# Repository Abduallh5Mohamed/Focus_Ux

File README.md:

# FOCUS — ابدأ من هنا

## تجربة النسخة الحالية على Windows

لتشغيل الواجهة والـAPI محليًا مع الـGPU والأصول الموجودة، من غير تعديل التثبيت القديم:
**[خطوات التجربة المحلية](docs/LOCAL_WINDOWS_TRIAL.md)**.
الوضع شبه المباشر تجريبي ومقفول افتراضيًا؛ اختبارات الكود مش إثباتًا للأداء الحقيقي.

خطة تنفيذ للمطورين الأربعة، 29 أكتوبر 2026. **منتج Upload/PWA كامل في اليوم الأول، تحسين ومحاولة معالجة أثناء التسجيل في اليوم الثاني.**

الأقسام التالية خطة التنفيذ الأصلية والمراجع؛ التطبيق الحالي داخل `product/`.
ده مش إعلان جاهزية للنشر أو اجتياز تجربة الـGPU.

## ترتيب القراءة
1. [الخطة الكاملة](docs/00_MASTER_PLAN.md).
2. [ما نستخدمه من القديم وكيف ننقله](docs/01_LEGACY_AND_MIGRATION.md).
3. [العقود المشتركة](docs/02_CONTRACTS.md) — يثبتها الفريق في أول ساعة.
4. كل مطور يقرأ ملفه ويبدأ مستقلًا:
   - [Dev 1 — ML Worker](docs/DEV1_ML.md)
   - [Dev 2 — API والنشر](docs/DEV2_BACKEND.md)
   - [Dev 3 — PWA والإدخال](docs/DEV3_PWA.md)
   - [Dev 4 — النتيجة والدمج](docs/DEV4_RESULTS_INTEGRATION.md)
5. [النشر والتشغيل](docs/03_DEPLOYMENT.md) و[بوابة الوضع المباشر](docs/04_REALTIME_GATE.md).

## الموجود هنا
- `legacy_snapshot/`: نسخ صغيرة من السكريبتات والتقارير والنتائج المرجعية، لا تعدّلها.
- `legacy_manifest.json`: مصدر كل ملف وSHA256 للتحقق.
- `docs/`: المهام والعقود وخطة التسليم.

## الموجود أصلًا ولا نعيد تنزيله
- `A:/focus/.venv`: البيئة التشغيلية؛ افحصها قبل الاعتماد عليها، ولا تنسخها بين الأجهزة.
- `A:/focus/Dolphin`: الكود والأصول.
- `A:/focus/cache`: cache؛ افحص المسارات المستخدمة فعليًا للأوزان، ولا تفترض أن كل الأوزان هنا.
- `A:/focus/data/gt5`: بيانات المقارنة ومراجعها.
- `C:/Users/abdua/WorkBuddy AI/2026-10-27-00-17-28`: تقارير الاختبارات القديمة.

## مكان البناء المقترح
ابنوا داخل `A:/فوكس/product/` بمستودع Git جديد مستقل عن التجارب. لم تُنشأ هذه الخدمة أو فروع Git بواسطة كتابة الخطة. أول شخص يجهّز المستودع هو Dev 4، ويشارك الفريق عبر مستودع خاص إن متاح.

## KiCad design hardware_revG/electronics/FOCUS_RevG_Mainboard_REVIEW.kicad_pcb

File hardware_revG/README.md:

# FOCUS RevG review package

An original everyday-eyewear design direction for the FOCUS assistive-listening concept, with a separate engineering packaging screen. The styling image is visual only. **No hardware was built or measured; this is not a release candidate.**

## Open first

1. [Visual design direction](INDUSTRIAL_DESIGN_DIRECTION.md) and [viewer-right camera style concept](previews/FOCUS_RevG_camera_right_concept.png).
2. [Compact CAD assembly review](mechanical/compact_direction/RevG_assembly_review.svg), [native FreeCAD](mechanical/compact_direction/FOCUS_RevG_Compact_Packaging_Screen.FCStd), [STEP](mechanical/compact_direction/FOCUS_RevG_Compact_Packaging_Screen.step), and [check data](mechanical/compact_direction/cad_checks.json). The native file has saved GUI visibility/colors/isometric view; if regenerating geometry with FreeCADCmd, run `mechanical/compact_direction/make_view_ready.FCMacro` in the GUI again before delivery.
3. [Engineering change plan](REV_G_CHANGE_PLAN.md), [open issues](REV_G_ASSUMPTIONS_AND_OPEN_ISSUES.md), and [release blockers](docs/DFM_AND_RELEASE_BLOCKERS.md).
4. [Electronics status](electronics/ENGINEERING_STATUS.md), [KiCad schematic](electronics/FOCUS_RevG_Mainboard_REVIEW.kicad_sch), [KiCad PCB](electronics/FOCUS_RevG_Mainboard_REVIEW.kicad_pcb), [ERC](electronics/reports/ERC.rpt), [DRC](electronics/reports/DRC.rpt).
5. [Candidate BOM](BOM.csv), [cost model](COST_MODEL.md), and [test plan](TEST_PLAN.md).

## Critical result

The compact CAD lowered the **partial assumed** mass from 98.86 g to 90.51 g, but still breaches the 60 g target and 70 g conditional ceiling before required unweighed parts. Folding and antenna fit fail. The partial KiCad drawing fails ERC/DRC and is bench-sized. Neither CAD nor electronics is ready for fabrication; styling and engineering currently diverge.

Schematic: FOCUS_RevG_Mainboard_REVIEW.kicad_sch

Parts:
C1, C2, C3, C4, C21, C22: 100nF X7R 10V; C_0603_1608Metric; MPN UNSELECTED
C10, C11, C12, C13: 1uF X7R 10V AC coupling; C_0603_1608Metric; MPN UNSELECTED
C20: 10uF X7R 10V; C_0603_1608Metric; MPN UNSELECTED
J1: P4 PDM host OPEN GPIO map; PinHeader_1x05_P2.54mm_Vertical; MPN UNSELECTED
J2: External regulated AMP rail 3.0V; PinHeader_1x02_P2.54mm_Vertical; MPN UNSELECTED
J3: External DAC differential analog; PinHeader_1x05_P2.54mm_Vertical; MPN UNSELECTED
J4: Host control 3V3; watchdog OPEN; PinHeader_1x05_P2.54mm_Vertical; MPN UNSELECTED
J5: HARD MUTE dry-contact switch; PinHeader_1x02_P2.54mm_Vertical; MPN UNSELECTED
J6: EXTERNAL open drain supervisor; PinHeader_1x02_P2.54mm_Vertical; MPN UNSELECTED
J7: Left BTL floating pair; PinHeader_1x02_P2.54mm_Vertical; MPN UNSELECTED
J8: Right BTL floating pair; PinHeader_1x02_P2.54mm_Vertical; MPN UNSELECTED
MK1, MK2, MK3, MK4: IM69D130 4x3x1.2 mm; Infineon_PG-LLGA-5-1; MPN IM69D130V01XTSA1
R1: 33R clock damping candidate; R_0603_1608Metric; MPN UNSELECTED
R10, R12, R14, R16: 100k 1% attenuation; R_0603_1608Metric; MPN UNSELECTED
R11, R13, R15, R17: 1k 1% attenuation; R_0603_1608Metric; MPN UNSELECTED
R20, R21: 4k7 candidate I2C pullup; R_0603_1608Metric; MPN UNSELECTED
R22: 10k host enable isolation; R_0603_1608Metric; MPN UNSELECTED
R23: 47k DEFAULT MUTE pulldown; R_0603_1608Metric; MPN UNSELECTED
TP1: MIC_3V3; TestPoint_Pad_D1.0mm; MPN UNSELECTED
TP2: PDM_CLK; TestPoint_Pad_D1.0mm; MPN UNSELECTED
TP3: PDM_D01; TestPoint_Pad_D1.0mm; MPN UNSELECTED
TP4: PDM_D23; TestPoint_Pad_D1.0mm; MPN UNSELECTED
TP5: AMP_3V0; TestPoint_Pad_D1.0mm; MPN UNSELECTED
TP6: AMP_SDZ; TestPoint_Pad_D1.0mm; MPN UNSELECTED
TP7: GND; TestPoint_Pad_D1.0mm; MPN UNSELECTED
U1: TPA2016D2RTJR REVIEW RTJ pad drawing; QFN-20-1EP_4x4mm_P0.5mm_EP2.5x2.5mm; MPN TPA2016D2RTJR

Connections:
/AMP_3V0: C20.1, C21.1, C22.1, J2.1 (AMP_3V0), TP5.1, U1.4 (PVDDL), U1.5 (PVDDL), U1.11 (PVDDR), U1.12 (PVDDR), U1.13 (AVDD)
/AMP_SDZ: J5.1 (AMP_SDZ), J6.1 (AMP_SDZ), R22.2, R23.1, TP6.1, U1.18 (SDZ)
/ATT_LN: C11.1, R12.2, R13.1
/ATT_LP: C10.1, R10.2, R11.1
/ATT_RN: C13.1, R16.2, R17.1
/ATT_RP: C12.1, R14.2, R15.1
/CTRL_3V3: J4.1 (CTRL_3V3), R20.1, R21.1
/DAC_LN: J3.2 (DAC_LN), R12.1
/DAC_LP: J3.1 (DAC_LP), R10.1
/DAC_RN: J3.4 (DAC_RN), R16.1
/DAC_RP: J3.3 (DAC_RP), R14.1
/GND: C1.2, C2.2, C3.2, C4.2, C20.2, C21.2, C22.2, J1.2 (GND), J2.2 (GND), J3.5 (GND), J4.2 (GND), J5.2 (GND), J6.2 (GND), MK1.4 (SELECT), MK1.5 (GND), MK2.5 (GND), MK3.4 (SELECT), MK3.5 (GND), MK4.5 (GND), R11.2, R13.2, R15.2, R17.2, R23.2, TP7.1, U1.3 (AGND), U1.8 (PGND), U1.21 (EP_VERIFY_PAD)
/HOST_AUDIO_ENABLE: J4.5 (HOST_AUDIO_ENABLE), R22.1
/IN_LN: C11.2, U1.2 (INL-)
/IN_LP: C10.2, U1.1 (INL+)
/IN_RN: C13.2, U1.14 (INR-)
/IN_RP: C12.2, U1.15 (INR+)
/MIC_3V3: C1.1, C2.1, C3.1, C4.1, J1.1 (MIC_3V3), MK1.2 (VDD), MK2.2 (VDD), MK2.4 (SELECT), MK3.2 (VDD), MK4.2 (VDD), MK4.4 (SELECT), TP1.1
/OUT_LN: J7.2 (OUT_LN), U1.7 (OUTL-)
/OUT_LP: J7.1 (OUT_LP), U1.6 (OUTL+)
/OUT_RN: J8.2 (OUT_RN), U1.9 (OUTR-)
/OUT_RP: J8.1 (OUT_RP), U1.10 (OUTR+)
/PDM_CLK: MK1.3 (CLOCK), MK2.3 (CLOCK), MK3.3 (CLOCK), MK4.3 (CLOCK), R1.2, TP2.1
/PDM_CLK_HOST: J1.3 (PDM_CLK_HOST), R1.1
/PDM_D01: J1.4 (PDM_D01), MK1.1 (DATA), MK2.1 (DATA), TP3.1
/PDM_D23: J1.5 (PDM_D23), MK3.1 (DATA), MK4.1 (DATA), TP4.1
/SCL: J4.3 (SCL), R20.2, U1.17 (SCL)
/SDA: J4.4 (SDA), R21.2, U1.19 (SDA)

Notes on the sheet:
FOCUS RevG MAINBOARD REVIEW - PARTIAL SUBSYSTEM SCHEMATIC ONLY
Four-mic PDM + analog amplifier only. Host / USB / LTE / SIM / charger / battery / regulators / DAC / watchdog / independent limiter NOT implemented.
NO FABRICATION RELEASE. P4 GPIO map open. Power sources are external lab supplies. Unresolved pins are deliberately open; ERC is not forced clean.
Default mute: R23 pulls SDZ low. External switch J5 shorts SDZ to GND regardless of host. J6 watchdog hardware is REQUIRED but not designed.
100k/1k input attenuation is a provisional fixed gain bound, NOT a certified independent limiter. DAC range, max gain, transient and output tests remain OPEN.
BTL: OUT_LN and OUT_RN are active outputs. Never tie to ground or each other. Dummy loads only until output and contact calibration.
USB topology proposal: P4 USB-HS HOST -> powered USB2512B hub -> B0441 UVC camera + A7670E USB modem. Separate modem VBAT supply.
Power proposal: USB-C protection -> charger/power path <-> protected 1S pack+NTC -> 3.8V modem / host rails / 5V VBUS / audio rail. Not drawn circuitry.

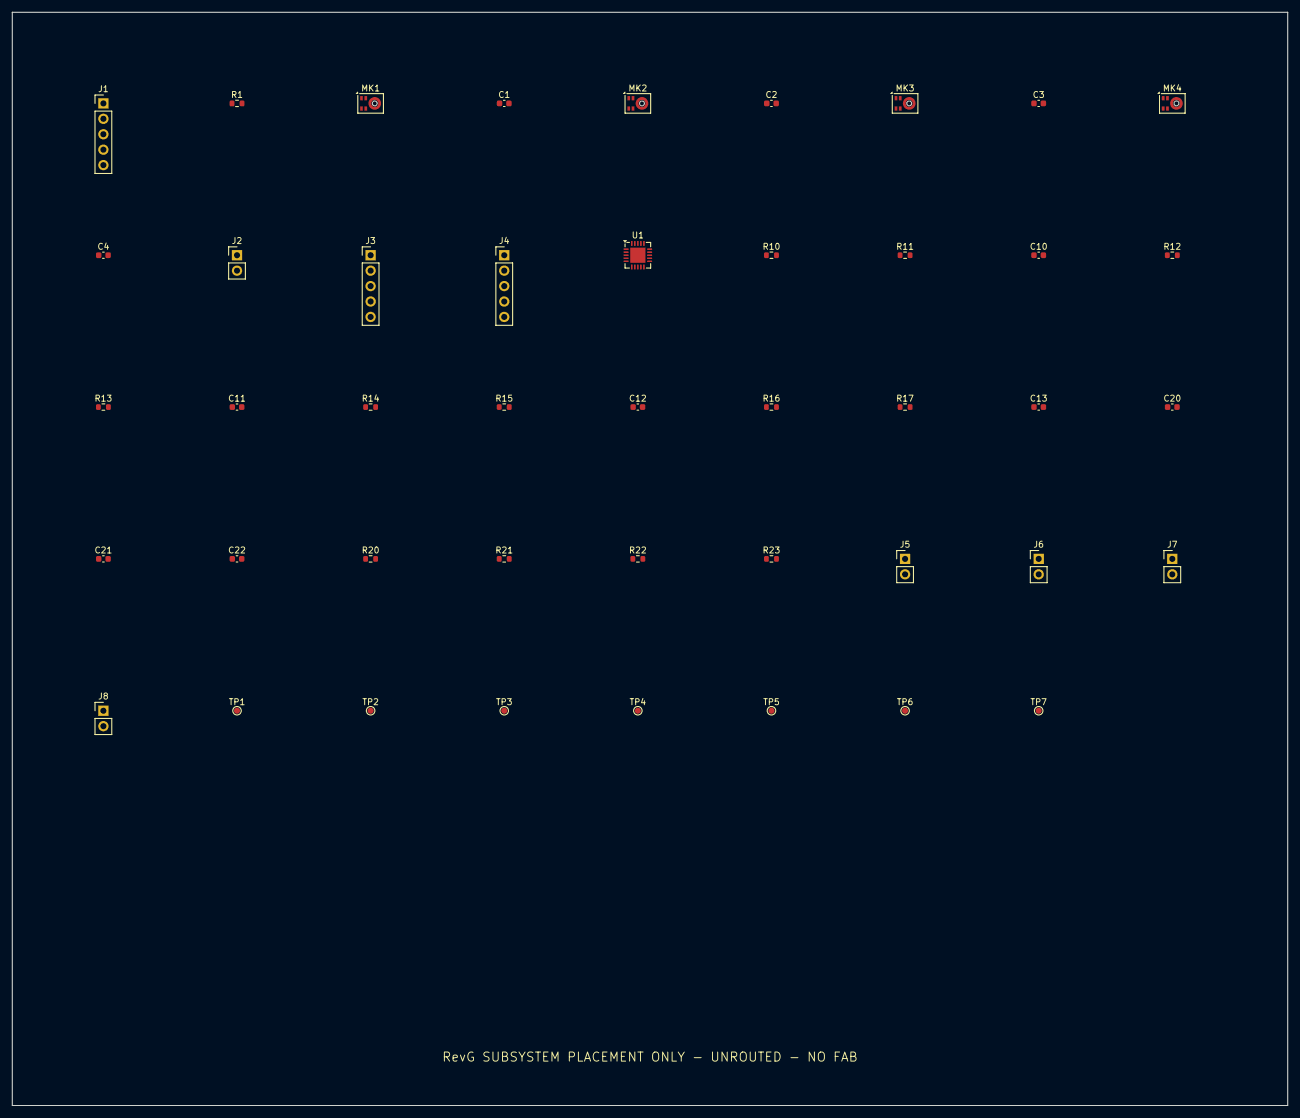
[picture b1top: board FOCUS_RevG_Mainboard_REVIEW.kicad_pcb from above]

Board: 2 copper layers, 210.0 x 180.0 mm, 44 parts (0 on the bottom side), 28 nets, no tracks yet.

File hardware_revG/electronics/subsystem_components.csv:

Reference,Value,MPN,Footprint,Datasheet,Review
J1,P4 PDM host OPEN GPIO map,UNSELECTED,Connector_PinHeader_2.54mm:PinHeader_1x05_P2.54mm_Vertical,,Bench header; production connector MPN and current rating unresolved
R1,33R clock damping candidate,UNSELECTED,Resistor_SMD:R_0603_1608Metric,,Value specified; manufacturer MPN/tolerance procurement OPEN
MK1,IM69D130 4x3x1.2 mm,IM69D130V01XTSA1,Sensor_Audio:Infineon_PG-LLGA-5-1,https://www.infineon.com/assets/row/public/documents/24/49/i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,Common clock; opposite SELECT within each data pair; bottom acoustic port MUST remain clear
C1,100nF X7R 10V,UNSELECTED,Capacitor_SMD:C_0603_1608Metric,,Value specified; manufacturer MPN/tolerance procurement OPEN
MK2,IM69D130 4x3x1.2 mm,IM69D130V01XTSA1,Sensor_Audio:Infineon_PG-LLGA-5-1,https://www.infineon.com/assets/row/public/documents/24/49/i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,Common clock; opposite SELECT within each data pair; bottom acoustic port MUST remain clear
C2,100nF X7R 10V,UNSELECTED,Capacitor_SMD:C_0603_1608Metric,,Value specified; manufacturer MPN/tolerance procurement OPEN
MK3,IM69D130 4x3x1.2 mm,IM69D130V01XTSA1,Sensor_Audio:Infineon_PG-LLGA-5-1,https://www.infineon.com/assets/row/public/documents/24/49/i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,Common clock; opposite SELECT within each data pair; bottom acoustic port MUST remain clear
C3,100nF X7R 10V,UNSELECTED,Capacitor_SMD:C_0603_1608Metric,,Value specified; manufacturer MPN/tolerance procurement OPEN
MK4,IM69D130 4x3x1.2 mm,IM69D130V01XTSA1,Sensor_Audio:Infineon_PG-LLGA-5-1,https://www.infineon.com/assets/row/public/documents/24/49/i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,Common clock; opposite SELECT within each data pair; bottom acoustic port MUST remain clear
C4,100nF X7R 10V,UNSELECTED,Capacitor_SMD:C_0603_1608Metric,,Value specified; manufacturer MPN/tolerance procurement OPEN
J2,External regulated AMP rail 3.0V,UNSELECTED,Connector_PinHeader_2.54mm:PinHeader_1x02_P2.54mm_Vertical,,Bench header; production connector MPN and current rating unresolved
J3,External DAC differential analog,UNSELECTED,Connector_PinHeader_2.54mm:PinHeader_1x05_P2.54mm_Vertical,,Bench header; production connector MPN and current rating unresolved
J4,Host control 3V3; watchdog OPEN,UNSELECTED,Connector_PinHeader_2.54mm:PinHeader_1x05_P2.54mm_Vertical,,Bench header; production connector MPN and current rating unresolved
U1,TPA2016D2RTJR REVIEW RTJ pad drawing,TPA2016D2RTJR,Package_DFN_QFN:QFN-20-1EP_4x4mm_P0.5mm_EP2.5x2.5mm,https://www.ti.com/lit/ds/symlink/tpa2016d2.pdf,Pins16/20 unresolved and intentionally OPEN. EP footprint provisional pending RTJ manufacturer land pattern; NOT RELEASED
R10,100k 1% attenuation,UNSELECTED,Resistor_SMD:R_0603_1608Metric,,Value specified; manufacturer MPN/tolerance procurement OPEN
R11,1k 1% attenuation,UNSELECTED,Resistor_SMD:R_0603_1608Metric,,Value specified; manufacturer MPN/tolerance procurement OPEN
C10,1uF X7R 10V AC coupling,UNSELECTED,Capacitor_SMD:C_0603_1608Metric,,Value specified; manufacturer MPN/tolerance procurement OPEN
R12,100k 1% attenuation,UNSELECTED,Resistor_SMD:R_0603_1608Metric,,Value specified; manufacturer MPN/tolerance procurement OPEN
R13,1k 1% attenuation,UNSELECTED,Resistor_SMD:R_0603_1608Metric,,Value specified; manufacturer MPN/tolerance procurement OPEN
C11,1uF X7R 10V AC coupling,UNSELECTED,Capacitor_SMD:C_0603_1608Metric,,Value specified; manufacturer MPN/tolerance procurement OPEN
R14,100k 1% attenuation,UNSELECTED,Resistor_SMD:R_0603_1608Metric,,Value specified; manufacturer MPN/tolerance procurement OPEN
R15,1k 1% attenuation,UNSELECTED,Resistor_SMD:R_0603_1608Metric,,Value specified; manufacturer MPN/tolerance procurement OPEN
C12,1uF X7R 10V AC coupling,UNSELECTED,Capacitor_SMD:C_0603_1608Metric,,Value specified; manufacturer MPN/tolerance procurement OPEN
R16,100k 1% attenuation,UNSELECTED,Resistor_SMD:R_0603_1608Metric,,Value specified; manufacturer MPN/tolerance procurement OPEN
R17,1k 1% attenuation,UNSELECTED,Resistor_SMD:R_0603_1608Metric,,Value specified; manufacturer MPN/tolerance procurement OPEN
C13,1uF X7R 10V AC coupling,UNSELECTED,Capacitor_SMD:C_0603_1608Metric,,Value specified; manufacturer MPN/tolerance procurement OPEN
C20,10uF X7R 10V,UNSELECTED,Capacitor_SMD:C_0603_1608Metric,,Value specified; manufacturer MPN/tolerance procurement OPEN
C21,100nF X7R 10V,UNSELECTED,Capacitor_SMD:C_0603_1608Metric,,Value specified; manufacturer MPN/tolerance procurement OPEN
C22,100nF X7R 10V,UNSELECTED,Capacitor_SMD:C_0603_1608Metric,,Value specified; manufacturer MPN/tolerance procurement OPEN
R20,4k7 candidate I2C pullup,UNSELECTED,Resistor_SMD:R_0603_1608Metric,,Value specified; manufacturer MPN/tolerance procurement OPEN
R21,4k7 candidate I2C pullup,UNSELECTED,Resistor_SMD:R_0603_1608Metric,,Value specified; manufacturer MPN/tolerance procurement OPEN
R22,10k host enable isolation,UNSELECTED,Resistor_SMD:R_0603_1608Metric,,Value specified; manufacturer MPN/tolerance procurement OPEN
R23,47k DEFAULT MUTE pulldown,UNSELECTED,Resistor_SMD:R_0603_1608Metric,,Value specified; manufacturer MPN/tolerance procurement OPEN
J5,HARD MUTE dry-contact switch,UNSELECTED,Connector_PinHeader_2.54mm:PinHeader_1x02_P2.54mm_Vertical,,Bench header; production connector MPN and current rating unresolved
J6,EXTERNAL open drain supervisor,UNSELECTED,Connector_PinHeader_2.54mm:PinHeader_1x02_P2.54mm_Vertical,,Bench header; production connector MPN and current rating unresolved
J7,Left BTL floating pair,UNSELECTED,Connector_PinHeader_2.54mm:PinHeader_1x02_P2.54mm_Vertical,,Bench header; production connector MPN and current rating unresolved
J8,Right BTL floating pair,UNSELECTED,Connector_PinHeader_2.54mm:PinHeader_1x02_P2.54mm_Vertical,,Bench header; production connector MPN and current rating unresolved
TP1,MIC_3V3,UNSELECTED,TestPoint:TestPoint_Pad_D1.0mm,,Probe pad; test instrument loading must be considered
TP2,PDM_CLK,UNSELECTED,TestPoint:TestPoint_Pad_D1.0mm,,Probe pad; test instrument loading must be considered
TP3,PDM_D01,UNSELECTED,TestPoint:TestPoint_Pad_D1.0mm,,Probe pad; test instrument loading must be considered
TP4,PDM_D23,UNSELECTED,TestPoint:TestPoint_Pad_D1.0mm,,Probe pad; test instrument loading must be considered
TP5,AMP_3V0,UNSELECTED,TestPoint:TestPoint_Pad_D1.0mm,,Probe pad; test instrument loading must be considered
TP6,AMP_SDZ,UNSELECTED,TestPoint:TestPoint_Pad_D1.0mm,,Probe pad; test instrument loading must be considered
TP7,GND,UNSELECTED,TestPoint:TestPoint_Pad_D1.0mm,,Probe pad; test instrument loading must be considered

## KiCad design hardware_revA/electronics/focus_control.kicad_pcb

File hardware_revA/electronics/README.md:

# FOCUS wired control carrier — RevA engineering prototype

Open `focus_control.kicad_pro` in KiCad 10.0.7. Native schematic and routed PCB are provided. `schematic.pdf` and `pcb_preview.svg` are convenience previews. `focus_control_board.step` is the **bare carrier PCB** mechanical reference, not a complete validated assembly.

## Architecture and scope

The original Raspberry Pi Pico H (RP2040, order SC0917) is plugged into two female sockets. It supplies USB serial/CDC **button events only**, and one status LED. It does not process video or audio. Its own USB connector attaches to the external host. The UVC camera with integrated microphone attaches directly to the host or powered USB hub on a separate cable. The carrier has no high-speed USB traces, audio circuit, battery, radio or custom power supply. All unused Pico pins remain isolated. Never connect the camera to GPIO or the control headers.

## Electrical pin map

| Function | Pico physical pin | GPIO | Carrier |
|---|---:|---|---|
| Ground | 3 | GND | J1.3, J3.2, J4.2, D1.1 |
| Select target | 4 | GP2 | J1.4 to J3.1; normally-open external switch to J3.2 |
| Stop/mute command | 5 | GP3 | J1.5 to J4.1; normally-open external switch to J4.2 |
| Status LED | 6 | GP4 | J1.6 to R1.1; R1.2 to D1.2(anode); D1.1 cathode to ground |

J1 socket n maps to physical Pico pin n, on the **bottom row** with USB pointing left. J2 socket n maps to physical Pico pin `41-n`, on the **top row** with USB pointing left. J2 has no connected carrier nets. Module component-side top view: USB faces left along negative X. Inserting Pico backward may not immediately power the carrier, but violates the design; check physical pin1 at(8.37,24.89) before power. Inputs require firmware internal pullups and software debounce (start20ms, then verify). This is an unprotected internal dry-contact interface; no external voltage input. Stop/mute is a software request; it is **not** a safety-certified or electrically hard audio disconnect.

R1=1k: at GPIO3.3V, LED current `(3.3-Vf)/1000`; even a shorted LED draws at most3.3mA through resistor. Actual brightness and Vf require the chosen LED sample. No external power is connected to Pico VBUS/VSYS/3V3 pins by this carrier.

## Mechanical interface

- PCB XY extent0..65 by0..32mm; nominal finished thickness1.6mm. KiCad top view origin upper-left. Actual exported STEP was read with FreeCAD: X0..65,Y-32..0,Z0..1.51mm. The dielectric body omits the surface-layer contribution to nominal1.6mm; reserve the full nominal thickness in mechanical tolerances. Normalize STEP as `u=STEP_X,v=-STEP_Y` before applying board-layout coordinates. This axis conversion is not a physical board reflection.
- Four NPTH holes, diameter2.4mm, centers(3,3),(62,3),(3,29),(62,29)mm.
- Pico board nominal51x21mm; target envelope x7..58,y5.5..26.5. Socket rows: **J1 y24.89 (physical1..20),J2 y7.11 (physical40..21)**; socket pin1 of each atx8.37; pitch2.54mm along+X, socket pin20x56.63. This matches17.78mm row spacing and48.26mm pin span. All40 socket pads were compared to the rotated stock Pico module footprint; see `physical_orientation_check.json` and `PHYSICAL_ORIENTATION.md`.
- J3 select header pads(61,8),(61,10.54); J4 stop pads(61,21.46),(61,24). External switches do not have fixed PCB positions.
- LED cathode pad(3,8), anode(3,10.54). R1 pads(3,19),(3,26.62).
- Housing must preserve USB plug/cable access from the left at y16mm. USB plug shape and minimum cable bend radius are still procurement-dependent.
- Allow a **20mm design envelope above PCB bottom** for sockets/Pico/connector soldering tolerances. This is a conservative design allowance, not a measured or certified assembled stack. Confirm real mating engagement, male-header plastic height, debug connector clearance and LED mounting height before closing the enclosure. Bare STEP omits these components.
- Generic populated STEP connector tails extend approximately1.505mm below the exported board origin; provide at least2mm underside clearance as a draft allowance, then verify chosen parts and trimmed solder joints. Generic model LED bbox: X1.1..4.9,Y-11.17..-7.77,Z-0.905..9.895mm; this confirms negative STEP-Y conversion. Generic sockets reachZ10.095mm before fitting Pico; assembled Pico/socket height remains procurement-dependent.

## Verification performed

KiCad CLI10.0.7:

- Schematic ERC: **0 errors,0 warnings** (`erc.rpt`).
- PCB DRC: **0 violations,0 unconnected items** (`drc.rpt`), default0.2mm clearance; routed tracks0.3mm; no vias in final routing.
- KiCad DRC with **schematic parity enabled:0 footprint/net parity issues** (`drc_parity.rpt`). Symbol UUID paths and full library IDs are assigned; intentional NC pads have their matching isolated nets; mounting holes are marked board-only/excluded from BOM and position files.
- Exported schematic connected nets compared to PCB pad memberships: **5/5 equal**, `connectivity_check.json`.
- Physical pin orientation compared independently to KiCad's stock original-Pico-compatible module footprint: **40/40 coordinates equal**, `physical_orientation_check.json`. See orientation report for the corrected initial row-mapping mistake; ERC alone could not catch it.
- Gerber layers, Excellon drill, PDF schematic and bare-board STEP exported successfully.

The schematic uses local **passive carrier symbols** for the sockets, resistor and LED; ERC therefore checks carrier connections, not the Pico internals or correctness of firmware/power sequencing. NC marks are deliberate. This cannot replace electrical prototype testing. The module is an external assembly listed separately in BOM; four mechanical mounting holes are board-only. Custom pad-net equality and KiCad schematic-parity mode both passed.

PCB embeds stock footprint geometry and refers to standard KiCad10 libraries (`Connector_PinSocket_2.54mm`, `Connector_PinHeader_2.54mm`, `Resistor_THT`, `LED_THT`). Installed `${KICAD10_3DMODEL_DIR}` STEP models resolve and exported successfully into `carrier_generic_components.step`. Those models show generic sockets/headers/LED/resistor, **not supplier-specific verified parts and not the Pico module**. `Focus.kicad_sym` and project-local `sym-lib-table` are included so schematic symbols do not require external installation.

## Manufacturing status

`manufacturing/` contains prototype fabrication outputs only. Do not order production as a released wearable design. The routed board has no intentional unrouted nets, but connector supplier drawings, exact switch and LED selection, socket mate height, real mechanical fit, USB throughput/power budget and assembled electrical tests are pending. Generic KiCad footprints do not establish supplier compatibility. All unresolved MPNs are explicitly marked in BOM.csv.

Bare-PCB draft spec:2-layer FR4,65x32mm,1.6mm,1oz copper nominal, soldermask both sides, no controlled-impedance requirement (no high-speed signal routed). Factory must review NPTH/PTH processing and supplied drill. No impedance or safety certification claimed.

## First assembled-unit test (not yet performed)

1. Inspect board and verify no shorts between connected GPIO nets and GND before installing module.
2. With module disconnected, meter J3/J4: normally open switch only, no foreign voltage.
3. Plug correctly oriented Pico H; USB power from current-limited host/hub. Confirm boots and CDC enumerates before connecting audio pipeline.
4. Confirm each button's GPIO reads high released/low pressed, firmware debounces and host receives the correct event. Verify LED operation.
5. Connect UVC camera independently, enumerate actual audio/video modes; verify microphone present on purchased camera variant. Measure stream timestamps and host load.
6. Measure end-to-end audio latency, electrical current, surface temperature and behavior on unplug/failure. Test wired headset volume conservatively; the carrier does not amplify or limit audio.

## Primary references

- [Original Raspberry Pi Pico datasheet](https://datasheets.raspberrypi.com/pico/pico-datasheet.pdf): module dimensions/pinout, GPIO and power information. Datasheet is the authoritative source; pin labels cross-checked.
- [Raspberry Pi Pico documentation](https://www.raspberrypi.com/documentation/microcontrollers/pico-series.html): Pico H module and header distinction.
- [Samtec SSW-120-01-G-S candidate](https://www.samtec.com/products/ssw-120-01-g-s): require series print review before final design-in.
- [Kingbright WP3A8GD candidate](https://www.kingbrightusa.com/images/catalog/SPEC/WP3A8GD.pdf): candidate LED; confirm purchased part and footprint compatibility.

## Reproduce

Run `A:/Kicad/bin/python.exe build_carrier.py`, then KiCad CLI ERC/DRC/export. Run schematic XML export followed by `A:/Kicad/bin/python.exe verify_netlist.py`. Generator overwrites local design files only; preserve manual edits separately before regeneration.

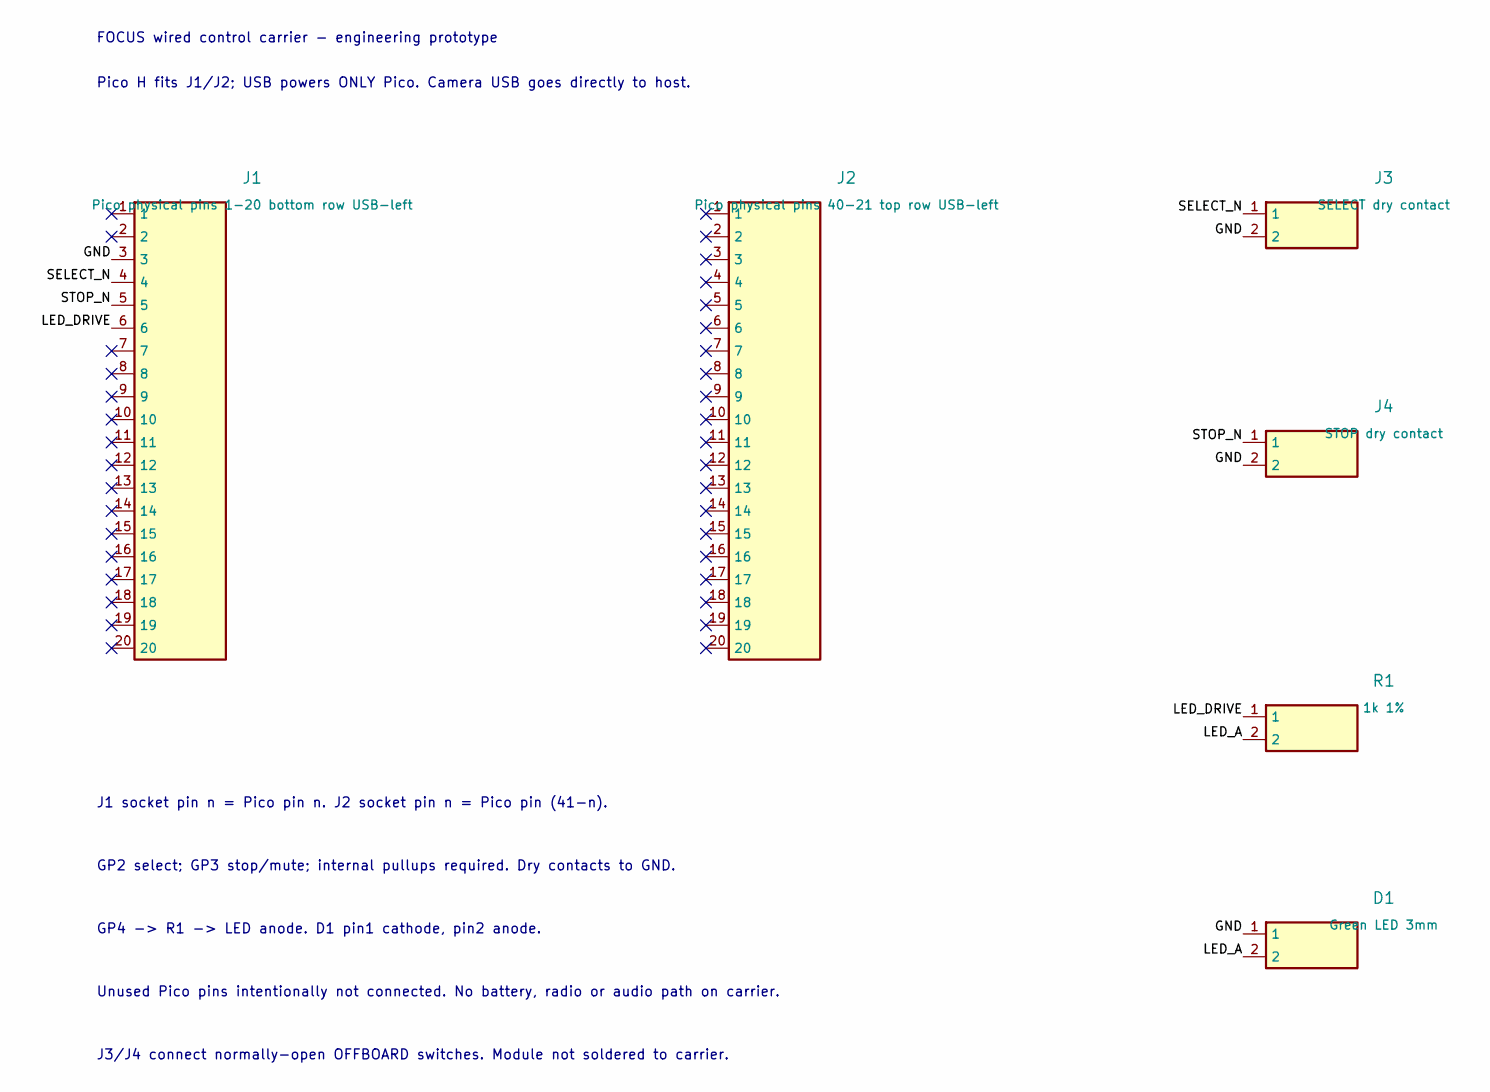
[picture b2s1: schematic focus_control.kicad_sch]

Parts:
D1: Green LED 3mm; LED_D3.0mm
J1: Pico physical pins 1-20 bottom row USB-left; PinSocket_1x20_P2.54mm_Vertical
J2: Pico physical pins 40-21 top row USB-left; PinSocket_1x20_P2.54mm_Vertical
J3: SELECT dry contact; PinHeader_1x02_P2.54mm_Vertical
J4: STOP dry contact; PinHeader_1x02_P2.54mm_Vertical
R1: 1k 1%; R_Axial_DIN0207_L6.3mm_D2.5mm_P7.62mm_Horizontal

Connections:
/GND: D1.1, J1.3, J3.2, J4.2
/LED_A: D1.2, R1.2
/LED_DRIVE: J1.6, R1.1
/SELECT_N: J1.4, J3.1
/STOP_N: J1.5, J4.1

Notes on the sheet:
FOCUS wired control carrier - engineering prototype
Pico H fits J1/J2; USB powers ONLY Pico. Camera USB goes directly to host.
J1 socket pin n = Pico pin n. J2 socket pin n = Pico pin (41-n).
GP2 select; GP3 stop/mute; internal pullups required. Dry contacts to GND.
GP4 -> R1 -> LED anode. D1 pin1 cathode, pin2 anode.
Unused Pico pins intentionally not connected. No battery, radio or audio path on carrier.
J3/J4 connect normally-open OFFBOARD switches. Module not soldered to carrier.

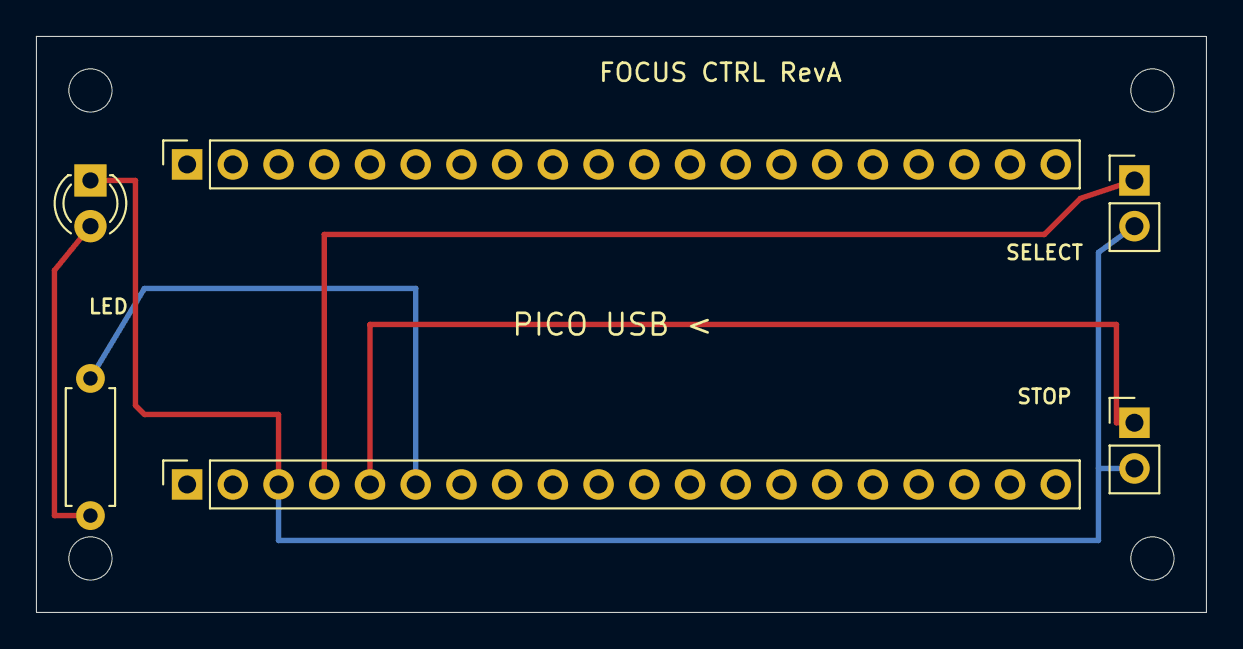
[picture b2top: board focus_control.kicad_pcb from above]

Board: 2 copper layers, 65.0 x 32.0 mm, 10 parts (0 on the bottom side), 5 nets.

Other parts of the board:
H1, H2, H3, H4: NPTH2.4

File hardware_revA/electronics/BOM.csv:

References,Quantity,Description,MPN_or_requirement,Status
U_module_external,1,Raspberry Pi Pico H RP2040 module,SC0917,Official original Pico H required; procurement and physical sample pending
J1 J2,2,1x20 female socket 2.54mm through-hole,Samtec SSW-120-01-G-S candidate,Series drawing and mate depth must be checked against Pico H before purchase; generic KiCad footprint is not supplier-approved
J3 J4,2,1x02 male header vertical 2.54mm,UNRESOLVED MPN,Choose <=5.08x2.54mm body and verify 1mm plated hole compatibility
R1,1,1k ohm 1 percent axial resistor 0.25W,UNRESOLVED MPN,Body <=6.3x2.5mm; lead formed to7.62mm; LED current max3.3mA even if LED short
D1,1,Green3mm through-hole LED,Kingbright WP3A8GD candidate,Verify lead pitch2.54mm and cathode before procurement; no assumed measured brightness
SW_SELECT SW_STOP,2,Offboard momentary normally-open dry-contact switch,UNRESOLVED MPN,Connect across J3 or J4; do not inject external voltage; enclosure holes not released
CABLE_CONTROLS,2,Two-wire insulated harness with mating connector,UNRESOLVED MPN,Short internal enclosure harness only; no exposed user electrical contacts
PCB,1,65x32x1.6mm two-layer FR4 carrier,Custom focus_control RevA,2.4mm NPTH4; minimum design track0.3mm; no battery or USB routing
FASTENERS,4,M2 fastener sets and insulating standoffs,UNRESOLVED lengths,Select after physical stack measurement; 2.4mm board holes

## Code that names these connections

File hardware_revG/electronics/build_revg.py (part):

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    add(ref,value,[('1','1','P'),('2','2','P')],{'1':a,'2':b},'Capacitor_SMD:C_0603_1608Metric' if cap else 'Resistor_SMD:R_0603_1608Metric',loc,notes='Value specified; manufacturer MPN/tolerance procurement OPEN')
micurl='https://www.infineon.com/assets/row/public/documents/24/49/infineon-im69d130-datasheet-en.pdf'
ampurl='https://www.ti.com/lit/ds/symlink/tpa2016d2.pdf'
hdr('J1','P4 PDM host OPEN GPIO map',['MIC_3V3','GND','PDM_CLK_HOST','PDM_D01','PDM_D23'],(50,45))
passive('R1','33R clock damping candidate','PDM_CLK_HOST','PDM_CLK',(125,45))
for i in range(4):
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    passive('C'+str(i+1),'100nF X7R 10V','MIC_3V3','GND',(50+i*90,120),True)
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hdr('J3','External DAC differential analog',['DAC_LP','DAC_LN','DAC_RP','DAC_RN','GND'],(140,160))
hdr('J4','Host control 3V3; watchdog OPEN',['CTRL_3V3','GND','SCL','SDA','HOST_AUDIO_ENABLE'],(230,160))
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mapping={'1':'IN_LP','2':'IN_LN','3':'GND','4':'AMP_3V0','5':'AMP_3V0','6':'OUT_LP','7':'OUT_LN','8':'GND','9':'OUT_RN','10':'OUT_RP','11':'AMP_3V0','12':'AMP_3V0','13':'AMP_3V0','14':'IN_RN','15':'IN_RP','17':'SCL','18':'AMP_SDZ','19':'SDA','21':'GND'}
add('U1','TPA2016D2RTJR REVIEW RTJ pad drawing',pins,mapping,'Package_DFN_QFN:QFN-20-1EP_4x4mm_P0.5mm_EP2.5x2.5mm',(410,160),'TPA2016D2RTJR',ampurl,'Pins16/20 unresolved and intentionally OPEN. EP footprint provisional pending RTJ manufacturer land pattern; NOT RELEASED')
for i,ch in enumerate(['LP','LN','RP','RN']):
    passive('R'+str(10+i*2),'100k 1% attenuation','DAC_'+ch,'ATT_'+ch,(50+i*90,240))
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
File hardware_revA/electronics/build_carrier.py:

"""Reproducible KiCad 10 carrier source generator; no external Python packages."""
from pathlib import Path
import pcbnew as p, uuid, json, csv
ROOT=Path(__file__).resolve().parent
LIB=Path('A:/Kicad/share/kicad/footprints')
def uid():return str(uuid.uuid4())
def xy(x,y):return p.VECTOR2I(p.FromMM(x),p.FromMM(y))
b=p.BOARD(); b.GetDesignSettings().SetBoardThickness(p.FromMM(1.6))
nets={}
for name in ['GND','SELECT_N','STOP_N','LED_DRIVE','LED_A']:
 n=p.NETINFO_ITEM(b,'/'+name);b.Add(n);nets[name]=n
components=[]
def fp(ref,value,lib,name,x,y,angle=0,pinmap={}):
 f=p.FootprintLoad(str(LIB/(lib+'.pretty')),name)
 if not f:raise RuntimeError(name)
 f.SetFPID(p.LIB_ID(lib,name))
 f.SetReference(ref);f.SetValue(value);f.SetOrientationDegrees(angle);f.SetPosition(xy(x,y))
 f.Reference().SetVisible(False);f.Value().SetVisible(False)
 for pad in f.Pads():
  if pad.GetNumber() in pinmap:pad.SetNet(nets[pinmap[pad.GetNumber()]])
  else:
   nc=p.NETINFO_ITEM(b,f'unconnected-({ref}-Pad{pad.GetNumber()})');b.Add(nc);pad.SetNet(nc)
 b.Add(f);components.append((ref,value,lib+':'+name,x,y,angle,pinmap));return f
j1=fp('J1','Pico physical pins 1-20 bottom row USB-left','Connector_PinSocket_2.54mm','PinSocket_1x20_P2.54mm_Vertical',8.37,24.89,90,{'3':'GND','4':'SELECT_N','5':'STOP_N','6':'LED_DRIVE'})
j2=fp('J2','Pico physical pins 40-21 top row USB-left','Connector_PinSocket_2.54mm','PinSocket_1x20_P2.54mm_Vertical',8.37,7.11,90)
j3=fp('J3','SELECT dry contact','Connector_PinHeader_2.54mm','PinHeader_1x02_P2.54mm_Vertical',61,8,0,{'1':'SELECT_N','2':'GND'})
j4=fp('J4','STOP dry contact','Connector_PinHeader_2.54mm','PinHeader_1x02_P2.54mm_Vertical',61,21.46,0,{'1':'STOP_N','2':'GND'})
d=fp('D1','Green LED 3mm','LED_THT','LED_D3.0mm',3,8,270,{'1':'GND','2':'LED_A'})
r=fp('R1','1k 1%','Resistor_THT','R_Axial_DIN0207_L6.3mm_D2.5mm_P7.62mm_Horizontal',3,19,270,{'1':'LED_DRIVE','2':'LED_A'})
for i,(x,y) in enumerate([(3,3),(62,3),(3,29),(62,29)],1):
 f=p.FOOTPRINT(b);f.SetReference('H'+str(i));f.SetValue('NPTH2.4');f.SetPosition(xy(x,y));f.Reference().SetVisible(False);f.Value().SetVisible(False)
 f.SetAttributes(p.FP_BOARD_ONLY|p.FP_EXCLUDE_FROM_BOM|p.FP_EXCLUDE_FROM_POS_FILES)
 pad=p.PAD(f);pad.SetAttribute(p.PAD_ATTRIB_NPTH);pad.SetShape(p.PAD_SHAPE_CIRCLE);pad.SetSize(xy(2.4,2.4));pad.SetDrillSize(xy(2.4,2.4));pad.SetLayerSet(p.LSET.AllCuMask());f.Add(pad);b.Add(f)
for a,c in [((0,0),(65,0)),((65,0),(65,32)),((65,32),(0,32)),((0,32),(0,0))]:
 s=p.PCB_SHAPE();s.SetShape(p.SHAPE_T_SEGMENT);s.SetStart(xy(*a));s.SetEnd(xy(*c));s.SetLayer(p.Edge_Cuts);s.SetWidth(p.FromMM(.05));b.Add(s)
def track(net,layer,points):
 for a,c in zip(points,points[1:]):
  t=p.PCB_TRACK(b);t.SetStart(xy(*a));t.SetEnd(xy(*c));t.SetWidth(p.FromMM(.3));t.SetLayer(layer);t.SetNet(nets[net]);b.Add(t)
track('SELECT_N',p.F_Cu,[(15.99,24.89),(15.99,11),(56,11),(58,9),(61,8)])
track('STOP_N',p.F_Cu,[(18.53,24.89),(18.53,16),(60,16),(60,21.46),(61,21.46)])
track('LED_DRIVE',p.B_Cu,[(21.07,24.89),(21.07,14),(6,14),(3,19)])
track('LED_A',p.F_Cu,[(3,26.62),(1,26.62),(1,13),(3,10.54)])
track('GND',p.F_Cu,[(13.45,24.89),(13.45,21),(6,21),(5.5,20.5),(5.5,8),(3,8)])
track('GND',p.B_Cu,[(13.45,24.89),(13.45,28),(59,28),(59,12),(61,10.54)])
track('GND',p.B_Cu,[(59,24),(61,24)])
# Legible fabrication labels; keep assembly data out of crowded silk areas.
for text,x,y,size in [('FOCUS CTRL RevA',38,2,1),('PICO USB <',32,16,1.2),('SELECT',56,12,.8),('STOP',56,20,.8),('LED',4,15,.8)]:
 t=p.PCB_TEXT(b);t.SetText(text);t.SetPosition(xy(x,y));t.SetTextSize(xy(size,size));t.SetTextThickness(p.FromMM(.15));t.SetLayer(p.F_SilkS);b.Add(t)
p.SaveBoard(str(ROOT/'focus_control.kicad_pcb'),b)
# Independently match physical module pin coordinates to every carrier socket pad.
module=p.FootprintLoad(str(LIB/'Module.pretty'),'RaspberryPi_Pico_Common_THT')
module.SetOrientationDegrees(90);module.SetPosition(xy(8.37,24.89))
modulepins={int(q.GetNumber()):q.GetPosition() for q in module.Pads() if q.GetNumber().isdigit() and 1<=int(q.GetNumber())<=40}
orientation=[]
for socket in [j1,j2]:
 for pad in socket.Pads():
  physical=int(pad.GetNumber()) if socket==j1 else 41-int(pad.GetNumber())
  target=modulepins[physical];actual=pad.GetPosition()
  assert actual==target,(socket.GetReference(),pad.GetNumber(),physical,actual,target)
  orientation.append({'socket':socket.GetReference(),'socket_pin':int(pad.GetNumber()),'pico_physical_pin':physical,'x_mm':p.ToMM(actual.x),'y_mm':p.ToMM(actual.y)})
(ROOT/'physical_orientation_check.json').write_text(json.dumps({'result':'PASS','reference':'KiCad10 Module:RaspberryPi_Pico_Common_THT rotated+90deg,physical1 located8.37,24.89; official USB-top pinout independently inspected','verified_pins':40,'pin_coordinates':orientation},indent=2))
# Native schematic: self-contained passive symbols, every unused socket pin NC.
rootuuid=uid();symbols=[];instances=[]
for ref,value,foot,x,y,ang,pinmap in components:
 count=20 if ref in ['J1','J2'] else 2
 name='Header20' if count==20 else ('Resistor' if ref=='R1' else 'LED' if ref=='D1' else 'Header2')
 if name not in [v[0] for v in symbols]:
  pins=''.join(f'(pin passive line (at -7.62 {-i*2.54:.4f} 0)(length 2.54)(name "{i+1}" (effects(font(size 1 1))))(number "{i+1}"(effects(font(size 1 1)))))' for i in range(count))
  definition=f'(symbol "Focus:{name}" (pin_names(offset 0.5))(in_bom yes)(on_board yes)(property "Reference" "J"(at 0 5 0)(effects(font(size 1 1))))(property "Value" "{name}"(at 0 2.5 0)(effects(font(size 1 1))))(symbol "{name}_0_1"(rectangle(start -5.08 1.27)(end 5.08 {-((count-1)*2.54+1.27):.4f})(stroke(width .254)(type default))(fill(type background))))(symbol "{name}_1_1" {pins}))'
  symbols.append((name,definition))
 sx,sy={'J1':(40,40),'J2':(105,40),'J3':(165,40),'J4':(165,65),'R1':(165,95),'D1':(165,120)}[ref]
 sx,sy=round(sx/1.27)*1.27,round(sy/1.27)*1.27
 ident=uid()
 for f in b.GetFootprints():
  if f.GetReference()==ref:f.SetPath(p.KIID_PATH('/'+rootuuid+'/'+ident))
 instances.append(f'(symbol(lib_id "Focus:{name}")(at {sx} {sy} 0)(unit 1)(in_bom yes)(on_board yes)(dnp no)(uuid "{ident}")(property "Reference" "{ref}"(at {sx+8} {sy-4} 0)(effects(font(size 1.27 1.27))))(property "Value" "{value}"(at {sx+8} {sy-1} 0)(effects(font(size 1 1))))(property "Footprint" "{foot}"(at {sx} {sy} 0)(effects(font(size 1 1))(hide yes)))'+''.join(f'(pin "{i+1}"(uuid "{uid()}"))' for i in range(count))+f'(instances(project "focus_control"(path "/{rootuuid}"(reference "{ref}")(unit 1)))))')
 for i in range(count):
  px,py=sx-7.62,sy+i*2.54; net=pinmap.get(str(i+1))
  if net:
   instances.append(f'(label "{net}"(at {px} {py} 0)(effects(font(size 1 1))(justify right bottom))(uuid "{uid()}"))')
  else:instances.append(f'(no_connect(at {px} {py})(uuid "{uid()}"))')
texts=[('FOCUS wired control carrier - engineering prototype',30,20),('Pico H fits J1/J2; USB powers ONLY Pico. Camera USB goes directly to host.',30,25),('J1 socket pin n = Pico pin n. J2 socket pin n = Pico pin (41-n).',30,105),('GP2 select; GP3 stop/mute; internal pullups required. Dry contacts to GND.',30,112),('GP4 -> R1 -> LED anode. D1 pin1 cathode, pin2 anode.',30,119),('Unused Pico pins intentionally not connected. No battery, radio or audio path on carrier.',30,126),('J3/J4 connect normally-open OFFBOARD switches. Module not soldered to carrier.',30,133)]
for text,x,y in texts:instances.append(f'(text "{text}"(at {x} {y} 0)(effects(font(size 1.1 1.1))(justify left))(uuid "{uid()}"))')
sch=f'(kicad_sch(version 20250114)(generator "focus_carrier_generator")(uuid "{rootuuid}")(paper "A4")(lib_symbols '+''.join(s[1] for s in symbols)+')'+''.join(instances)+')'
(ROOT/'focus_control.kicad_sch').write_text(sch,encoding='utf-8')
(ROOT/'Focus.kicad_sym').write_text('(kicad_symbol_lib(version 20250114)(generator "focus_carrier_generator")'+''.join(s[1].replace('(symbol "Focus:', '(symbol "') for s in symbols)+')')
(ROOT/'sym-lib-table').write_text('(sym_lib_table\n  (version 7)\n  (lib (name "Focus") (type "KiCad") (uri "${KIPRJMOD}/Focus.kicad_sym") (options "") (descr "Local carrier schematic symbols"))\n)\n')
(ROOT/'placement.json').write_text(json.dumps([{'reference':q[0],'value':q[1],'footprint':q[2],'x_mm':q[3],'y_mm':q[4],'rotation_deg':q[5],'net_mapping':q[6]} for q in components],indent=2))
(ROOT/'focus_control.kicad_pro').write_text('{}')
p.SaveBoard(str(ROOT/'focus_control.kicad_pcb'),b)
print('Created native schematic and routed PCB')
